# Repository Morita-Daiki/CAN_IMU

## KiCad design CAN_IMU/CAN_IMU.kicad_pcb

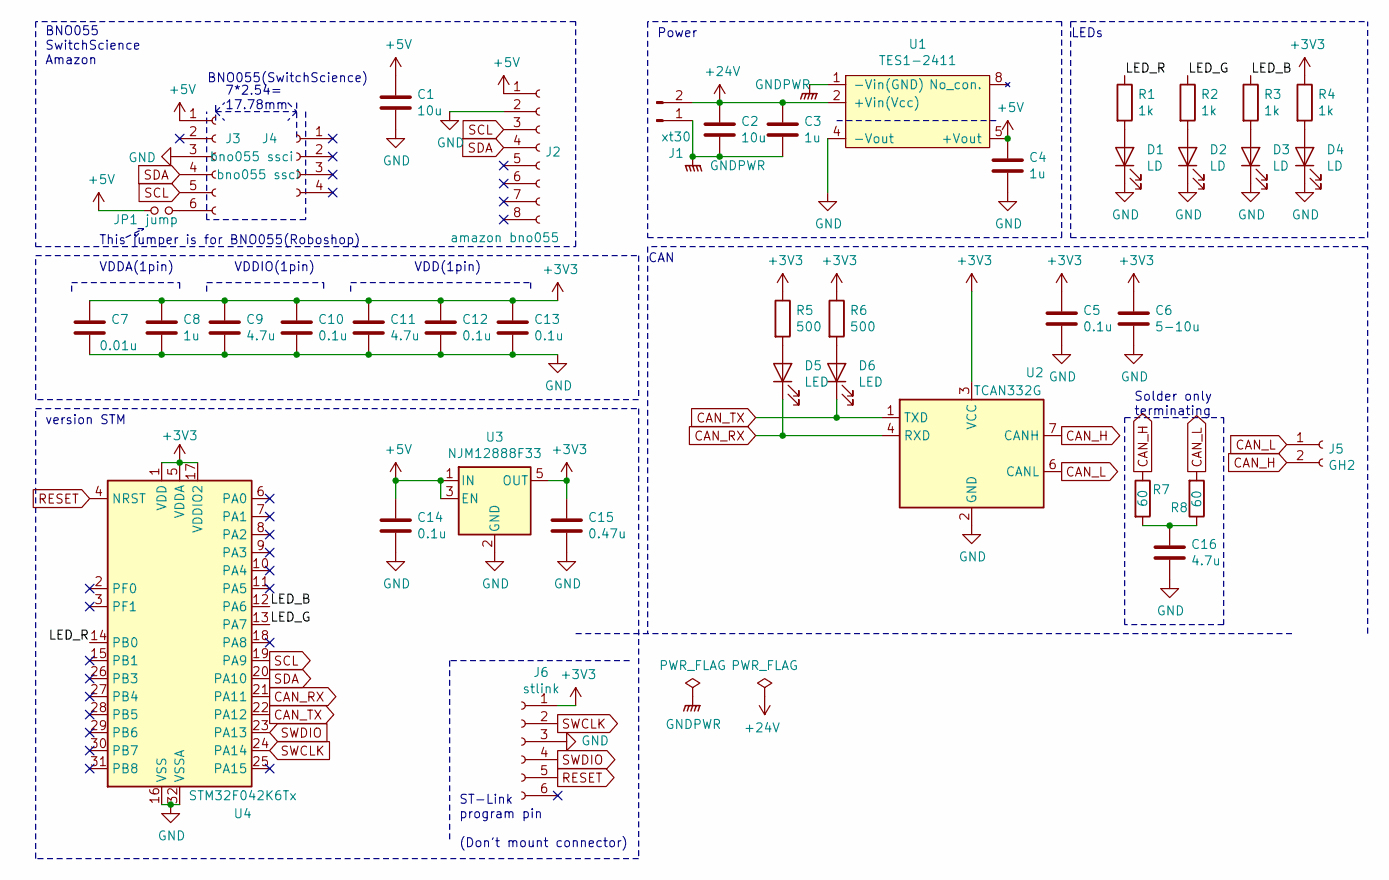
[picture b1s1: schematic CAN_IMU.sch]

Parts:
C1, C2: 10u; C_0603_1608Metric_Pad1.05x0.95mm_HandSolder
C3, C4, C8: 1u; C_0603_1608Metric_Pad1.05x0.95mm_HandSolder
C5, C10, C12, C13, C14: 0.1u; C_0603_1608Metric_Pad1.05x0.95mm_HandSolder
C6: 5-10u; C_0603_1608Metric_Pad1.05x0.95mm_HandSolder
C7: 0.01u; C_0603_1608Metric_Pad1.05x0.95mm_HandSolder
C9, C11, C16: 4.7u; C_0603_1608Metric_Pad1.05x0.95mm_HandSolder
C15: 0.47u; C_0603_1608Metric_Pad1.05x0.95mm_HandSolder
D1, D2, D3, D4: LD; LED_0603_1608Metric_Pad1.05x0.95mm_HandSolder
D5, D6: LED; LED_0603_1608Metric_Pad1.05x0.95mm_HandSolder
J1: xt30; AMASS_XT30PW-M_1x02_P2.50mm_Horizontal
J2: amazon bno055; PinSocket_1x08_P2.54mm_Vertical_SMD_Pin1Left
J3: bno055 ssci; PinSocket_1x06_P2.54mm_Vertical_SMD_Pin1Left
J4: bno055 ssci; PinSocket_1x04_P2.54mm_Vertical_SMD_Pin1Left
J5: GH2; JST_GH_SM02B-GHS-TB_1x02-1MP_P1.25mm_Horizontal
J6: stlink; PinHeader_1x06_P2.54mm_Vertical
JP1: jump; SolderJumper-2_P1.3mm_Open_RoundedPad1.0x1.5mm
R1, R2, R3, R4: 1k; R_0603_1608Metric_Pad1.05x0.95mm_HandSolder
R5, R6: 500; R_0603_1608Metric_Pad1.05x0.95mm_HandSolder
R7, R8: 60; R_0603_1608Metric_Pad1.05x0.95mm_HandSolder
U1: TES1-2411; TES1-single
U2: TCAN332G; SOIC-8_3.9x4.9mm_P1.27mm
U3: NJM12888F33; SOT-23-5
U4: STM32F042K6Tx; LQFP-32_7x7mm_P0.8mm

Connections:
+3V3: C5.1, C6.1, C7.1, C8.1, C9.1, C10.1, C11.1, C12.1, C13.1, C15.1, J6.1, R4.1, R5.1, R6.1, U2.3 (VCC), U3.5 (OUT), U4.1 (VDD), U4.5 (VDDA), U4.17 (VDDIO2)
+5V: C1.1, C4.1, C14.1, J2.1, J3.1, JP1.1, U1.5 (+Vout), U3.1 (IN), U3.3 (EN)
+24V: C2.1, C3.1, J1.2, U1.2 (+Vin(Vcc))
/LED_B: R3.1, U4.12 (PA6)
/LED_G: R2.1, U4.13 (PA7)
/LED_R: R1.1, U4.14 (PB0)
CAN_H: J5.2, R7.1, U2.7 (CANH)
CAN_L: J5.1, R8.2, U2.6 (CANL)
CAN_RX: D5.1 (K), U2.4 (RXD), U4.21 (PA11)
CAN_TX: D6.1 (K), U2.1 (TXD), U4.22 (PA12)
GND: C1.2, C4.2, C5.2, C6.2, C7.2, C8.2, C9.2, C10.2, C11.2, C12.2, C13.2, C14.2, C15.2, C16.2, D1.1 (K), D2.1 (K), D3.1 (K), D4.1 (K), J2.2, J3.3, J6.3, U1.4 (-Vout), U2.2 (GND), U3.2 (GND), U4.16 (VSS), U4.32 (VSSA)
GNDPWR: C2.2, C3.2, J1.1, U1.1 (-Vin(GND))
unnamed: C16.1, R7.2, R8.1
unnamed: D1.2 (A), R1.2
unnamed: D2.2 (A), R2.2
unnamed: D3.2 (A), R3.2
unnamed: D4.2 (A), R4.2
unnamed: D5.2 (A), R5.2
unnamed: D6.2 (A), R6.2
unnamed: J3.6, JP1.2
RESET: J6.5, U4.4 (NRST)
SCL: J2.3, J3.5, U4.19 (PA9)
SDA: J2.4, J3.4, U4.20 (PA10)
SWCLK: J6.2, U4.24 (PA14)
SWDIO: J6.4, U4.23 (PA13)

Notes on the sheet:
Solder only terminating
CAN
version STM
ST-Link program pin (Don't mount connector)
Power
BNO055 SwitchScience Amazon
7*2.54= 17.78mm
This jumper is for BNO055(Roboshop)
BNO055(SwitchScience)
LEDs
VDDA(1pin)
VDDIO(1pin)
VDD(1pin)

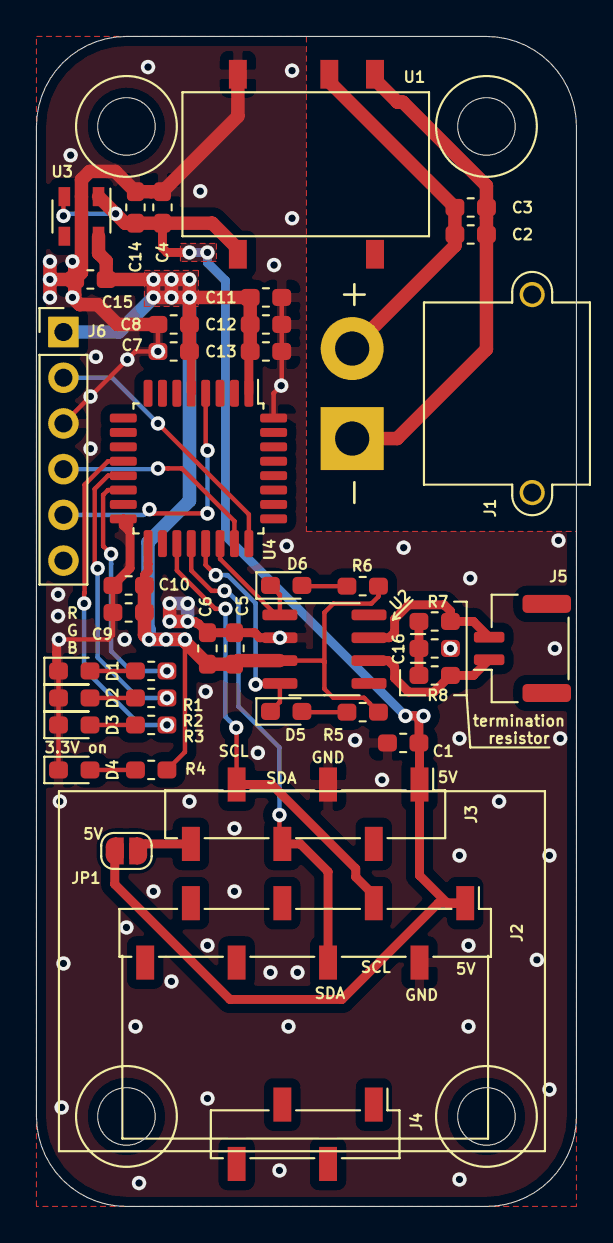
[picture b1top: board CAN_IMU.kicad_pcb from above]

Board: 2 copper layers, 30.0 x 65.0 mm, 41 parts (0 on the bottom side), 25 nets.

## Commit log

2019-12-03 CAN追加
2019-12-04 test
2019-12-04 3.3v reguretor
2019-12-04 move
2019-12-04 delete
2019-12-04 micon
2019-12-10 STMに変更
2019-12-11 一応完成
2019-12-11 ガーバー出力
2019-12-11 回路図プロット
